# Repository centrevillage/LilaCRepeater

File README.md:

# LilaCRepeater
Eurorack sample looping module driven by Daisy (https://www.electro-smith.com/daisy)

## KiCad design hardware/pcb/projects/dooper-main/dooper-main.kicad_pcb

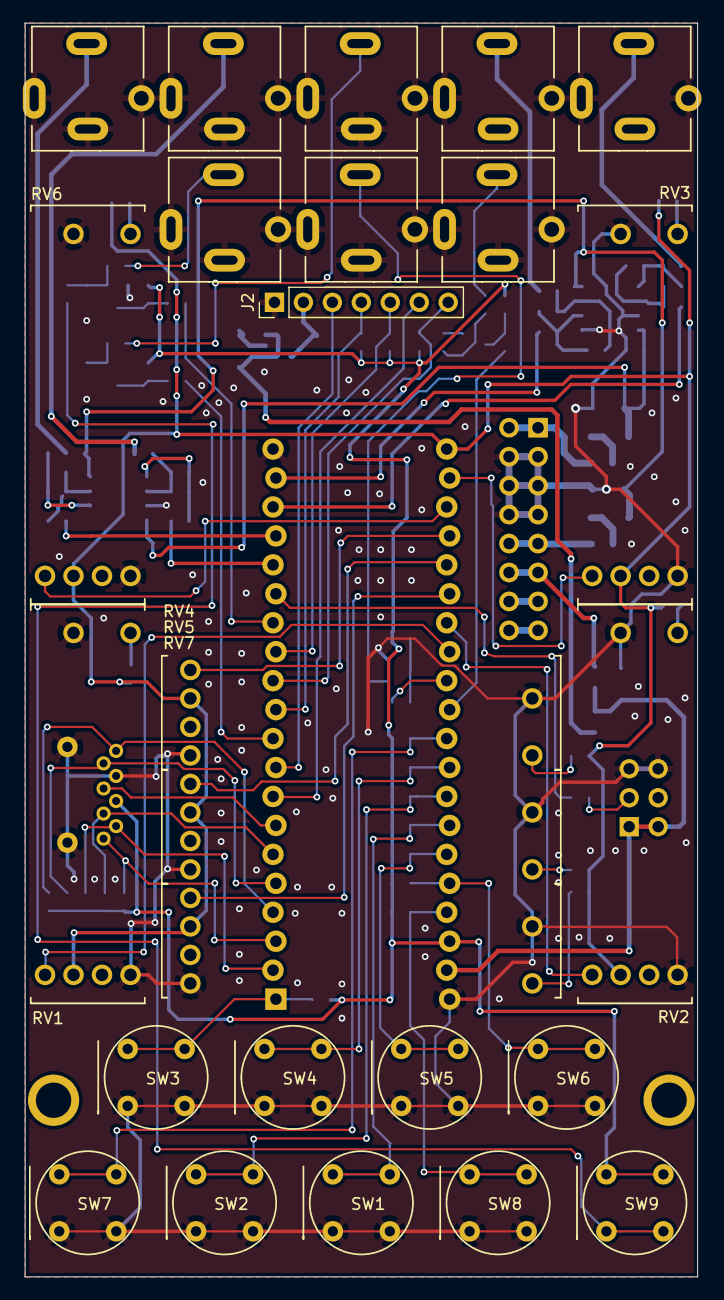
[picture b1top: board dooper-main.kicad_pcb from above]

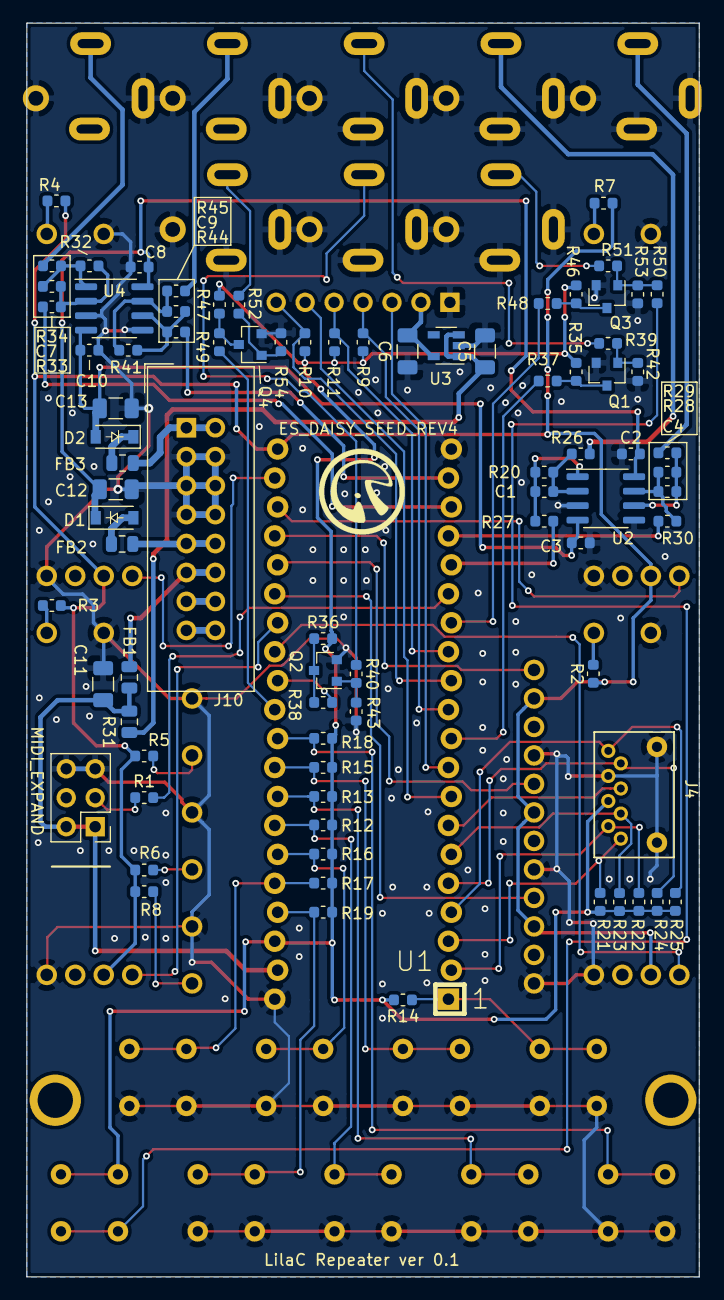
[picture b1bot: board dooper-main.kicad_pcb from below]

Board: 2 copper layers, 59.0 x 110.0 mm, 110 parts (83 on the bottom side), 83 nets.

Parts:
C1, C4, C7, C9: 18p; C_0603_1608Metric
C2, C3, C8, C10: 100n; C_0603_1608Metric
C5, C6, C11, C12, C13: 22u; C_1206_3216Metric
D1, D2: 1N5158; D_SOD-123_1n4148_mod
FB1, FB2, FB3: 600; R_0805_2012Metric
H1, H1#2: M3_Hole; M3_GND_HOLE_MINI
J1: Conn_02x03_Odd_Even; PinHeader_2x03_P2.54mm_Vertical
J2: Conn_01x07; PinHeader_1x07_P2.54mm_Vertical
J3, J5, J6, J7, J8, J9, J11, J12: PJ301BM; PJ301BM_oval_smallpad
J4: Micro_SD_Card; MICRO_SD_VERTICAL
J10: Conn_02x08_Odd_Even; IDC-Header_2x08_P2.54mm_Vertical
Q1, Q2, Q3, Q4: MMBT3904; SOT-23
R1: 47; R_0603_1608Metric
R2, R3, R4, R5, R6, R7, R8, R9, R10, R11, R12, R13, R14, R15, R16, R17, R18, R19, R20, R28, R33, R35, R36, R44, R46, R47: 10k; R_0603_1608Metric
R21, R22, R23, R24, R25: 47k; R_0603_1608Metric
R26, R29, R32, R39, R40, R41, R42, R43, R50, R51, R52, R53, R54: 100k; R_0603_1608Metric
R27, R30, R34, R37, R38, R45, R48, R49: 470; R_0603_1608Metric
R31: 10; R_0805_2012Metric
RV1, RV2, RV3, RV4, RV5, RV6, RV7: SLIDER; BOURNS_SLIDER_20mm
SW1, SW2, SW3, SW4, SW5, SW6, SW7, SW8, SW9: SW_Push; CandK_Comp_Button
U1: ES_DAISY_SEED_REV4; ES_DAISY_SEED
U2, U4: OPA2134; SOIC-8_3.9x4.9mm_P1.27mm
U3: LDK320; SOT-23-5

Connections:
+3.3VA: R2.1, R3.1, R4.1, R5.1, R6.1, R7.1, R8.1, RV1.1, RV2.1, RV3.1, RV4.1, RV5.1, RV6.1, RV7.1, U1.21
+3V3: J4.4, R9.1, R10.1, R11.1, R12.2, R13.2, R14.2, R15.2, R16.2, R17.2, R18.2, R19.2, R21.1, R22.1, R23.1, R24.1, R25.1, R35.2, R36.2, R46.2, R47.2, SW9.1, U1.38
+5V: C11.1, FB1.1, J1.1, J1.2, R31.2, U1.39
+12V: C2.2, C8.2, C12.1, D1.1, U2.8, U4.8
-12V: C3.2, C10.2, C13.2, D2.2, U2.4, U4.4
/CLEAR_BTN: R12.1, SW1.1, U1.34
/DG_AUDIO_IN_L: R27.1, U1.16
/DG_AUDIO_IN_R: R30.1, U1.17
/DG_AUDIO_OUT_L: R33.2, U1.18
/DG_AUDIO_OUT_R: R44.2, U1.19
/DRY_VOL: RV1.2, U1.28
/MUTE_BTN: R18.1, SW7.1, U1.31
/OLED_DC: J2.6, U1.8
/PAN: RV7.2, U1.26
/REC_TARGET_BTN: R13.1, SW2.1, U1.33
/REC_TRIG: R49.1, U1.30
/RESET_TRIG: R38.1, U1.29
/REVERSE_BTN: R19.1, SW8.1, U1.37
/RUN_TRIG: R48.1, U1.14
/SAMPLE_FDBK: RV6.2, U1.23
/SAMPLE_LENGTH: RV5.2, U1.25
/SAMPLE_SPEED: RV3.2, U1.22
/SAMPLE_START_POS: RV4.2, U1.24
/SD_CLK: J4.5, U1.7
/SD_CMD: J4.3, R23.2, U1.6
/SD_D0: J4.7, R24.2, U1.5
/SD_D1: J4.8, R25.2, U1.4
/SD_D2: J4.1, R21.2, U1.3
/SD_D3: J4.2, R22.2, U1.2
/SPI_MOSI: J2.4, R9.2, U1.11
/SPI_SCK: J2.3, U1.9
/SYNC_IN: R37.1, U1.10
/TRACK1_BTN: R14.1, SW3.1, U1.1
/TRACK2_BTN: R15.1, SW4.1, U1.32
/TRACK3_BTN: R16.1, SW5.1, U1.35
/TRACK4_BTN: R17.1, SW6.1, U1.36
/TRACK_VOL: RV2.2, U1.27
/USART_RX: R1.2, U1.15
/~OLED_CS: J2.7, R10.2, U1.12
/~OLED_RST: J2.5, R11.2, U1.13
GND: C2.1, C3.1, C5.2, C6.2, C8.1, C10.1, C11.2, C12.2, C13.1, J1.5, J1.6, J2.1, J3.1, J3.2, J3.3, J4.6, J4.9, J5.1, J5.2, J5.3, J6.1, J6.2, J7.1, J7.2, J7.3, J8.1, J8.2, J8.3, J9.1, J9.2, J10.3, J10.4, J10.5, J10.6, J10.7, J10.8, J11.1, J11.2, J11.3, J12.1, J12.2, J12.3, Q1.2, Q2.2, Q3.2, Q4.2, R42.1, R43.1, R53.1, R54.1, RV1.3, RV1.5, RV2.3, RV2.5, RV3.3, RV3.5, RV4.3, RV4.5, RV5.3, RV5.5, RV6.3, RV6.5, RV7.3, RV7.5, SW1.2, SW2.2, SW3.2, SW4.2, SW5.2, SW6.2, SW7.2, SW8.2, U1.20, U1.40, U2.3, U2.5, U3.2, U4.3, U4.5
unnamed: C1.1, R20.1, R27.2, U2.1
unnamed: C1.2, R20.2, R26.1, U2.2
unnamed: C4.1, R28.1, R30.2, U2.7
unnamed: C4.2, R28.2, R29.1, U2.6
unnamed: C5.1, R31.1, U3.1, U3.3
unnamed: C7.1, R32.1, R34.2, U4.1
unnamed: C7.2, R32.2, R33.1, U4.2
unnamed: C9.1, R41.1, R45.2, U4.7
unnamed: C9.2, R41.2, R44.1, U4.6
unnamed: D1.2, FB2.1
unnamed: D2.1, FB3.1
unnamed: FB1.2, J10.11, J10.12
unnamed: FB2.2, J10.9, J10.10
unnamed: FB3.2, J10.1, J10.2
unnamed: J1.3, R1.1
unnamed: J3.4, R29.2
unnamed: J5.4, R26.2
unnamed: J6.4, R45.1
unnamed: J7.4, R39.2
unnamed: J8.4, R40.2
unnamed: J9.4, R34.1
unnamed: J10.13, J10.14
unnamed: J10.15, J10.16
unnamed: J11.4, R51.2
unnamed: J12.4, R52.2
unnamed: Q1.1, R39.1, R42.2
unnamed: Q1.3, R35.1, R37.2
unnamed: Q2.1, R40.1, R43.2
unnamed: Q2.3, R36.1, R38.2
unnamed: Q3.1, R50.1, R51.1, R53.2
unnamed: Q3.3, R46.1, R48.2
unnamed: Q4.1, R52.1, R54.2
unnamed: Q4.3, R47.1, R49.2
unnamed: R2.2, RV1.4
unnamed: R3.2, RV2.4
unnamed: R4.2, RV3.4
unnamed: R5.2, RV4.4
unnamed: R6.2, RV5.4
unnamed: R7.2, RV6.4
unnamed: R8.2, RV7.4
unnamed: R50.2, SW9.2
OLED_VCC: C6.1, J2.2, U3.5

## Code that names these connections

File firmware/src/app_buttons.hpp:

#ifndef LR_APP_BUTTONS_H
#define LR_APP_BUTTONS_H

#include <igb_stm32/periph/gpio.hpp>
#include <igb_daisy/periph/gpio.hpp>
#include <igb_sdk/ui/button.hpp>
#include <functional>
#include <array>

using namespace igb::stm32;
using namespace igb::sdk;
using namespace igb::daisy;

enum class AppBtnId : uint8_t {
  track1 = 0,
  track2,
  track3,
  track4,
  mute,
  rec,
  clear,
  rev,
  run,

  size
};

constexpr uint8_t button_count = 9;

struct AppButtons {
  uint16_t state_bits = 0;
  std::function<void(AppBtnId, bool)> on_change;

// hardware version 0.3 ~
#if 1
  ButtonMatrix<GpioPin, 3, GpioPin, 3> btn_matrix {
    .in_pins = {
      GpioPin::newPin(daisy_pin_to_stm32_pin(DaisyGpioPinType::p29)),
      GpioPin::newPin(daisy_pin_to_stm32_pin(DaisyGpioPinType::p30)),
      GpioPin::newPin(daisy_pin_to_stm32_pin(DaisyGpioPinType::p31)),
    },
    .out_pins = {
      GpioPin::newPin(daisy_pin_to_stm32_pin(DaisyGpioPinType::p26)),
      GpioPin::newPin(daisy_pin_to_stm32_pin(DaisyGpioPinType::p27)),
      GpioPin::newPin(daisy_pin_to_stm32_pin(DaisyGpioPinType::p28))
    }
  };
#endif
  
// hardware version 0.2 ~
#if 0
  ButtonSingle<GpioPin> mute_btn {
    GpioPin::newPin(daisy_pin_to_stm32_pin(DaisyGpioPinType::p25))
  };

  ButtonMatrix<GpioPin, 4, GpioPin, 2> btn_matrix {
    .in_pins = {
      GpioPin::newPin(daisy_pin_to_stm32_pin(DaisyGpioPinType::p28)),
      GpioPin::newPin(daisy_pin_to_stm32_pin(DaisyGpioPinType::p29)),
      GpioPin::newPin(daisy_pin_to_stm32_pin(DaisyGpioPinType::p30)),
      GpioPin::newPin(daisy_pin_to_stm32_pin(DaisyGpioPinType::p31))
    },
    .out_pins = {
      GpioPin::newPin(daisy_pin_to_stm32_pin(DaisyGpioPinType::p26)),
      GpioPin::newPin(daisy_pin_to_stm32_pin(DaisyGpioPinType::p27))
    }
  };
#endif

// hardware version 0.1
#if 0
  // TODO: button matrix (fix hardware)
  ButtonSingle<GpioPin> mute_btn {
    GpioPin::newPin(daisy_pin_to_stm32_pin(DaisyGpioPinType::p25))
  };
  ButtonSingle<GpioPin> rec_btn {
    GpioPin::newPin(daisy_pin_to_stm32_pin(DaisyGpioPinType::p27))
  };
  ButtonSingle<GpioPin> clear_btn {
    GpioPin::newPin(daisy_pin_to_stm32_pin(DaisyGpioPinType::p28))
  };
  ButtonSingle<GpioPin> rev_btn {
    GpioPin::newPin(daisy_pin_to_stm32_pin(DaisyGpioPinType::p31))
  };
  // TODO: テンプレートパラメータでbool値を渡した時の挙動が変？
  //ButtonSingle<GpioPin, false> run_btn {
  ButtonSingle<GpioPin> run_btn {
    GpioPin::newPin(daisy_pin_to_stm32_pin(DaisyGpioPinType::p14))
  }; // pull down
  ButtonSingle<GpioPin> track1_btn {
    GpioPin::newPin(daisy_pin_to_stm32_pin(DaisyGpioPinType::p1))
  };
  ButtonSingle<GpioPin> track2_btn {
    GpioPin::newPin(daisy_pin_to_stm32_pin(DaisyGpioPinType::p26))
  };
  ButtonSingle<GpioPin> track3_btn {
    GpioPin::newPin(daisy_pin_to_stm32_pin(DaisyGpioPinType::p29))
  };
  ButtonSingle<GpioPin> track4_btn {
    GpioPin::newPin(daisy_pin_to_stm32_pin(DaisyGpioPinType::p30))
  };
#endif

  void init() {
// hardware version 0.3 ~
#if 1
    for (auto& in_pin : btn_matrix.in_pins) {
      in_pin.enable();
      in_pin.initInput(GpioPullMode::no, GpioSpeedMode::high);
    }
    for (auto& out_pin : btn_matrix.out_pins) {
      out_pin.enable();
      out_pin.initOutput(GpioOutputMode::pushpull, GpioSpeedMode::high);
    }
    btn_matrix.init();
#endif

// hardware version 0.2 ~
#if 0
    mute_btn.pin.enable();
    mute_btn.pin.initInput(GpioPullMode::UP, GpioSpeedMode::HIGH);

    for (auto& in_pin : btn_matrix.in_pins) {
      in_pin.enable();
      in_pin.initInput(GpioPullMode::NO, GpioSpeedMode::HIGH);
    }
    for (auto& out_pin : btn_matrix.out_pins) {
      out_pin.enable();
      out_pin.initOutput(GpioOutputMode::PUSHPULL, GpioSpeedMode::HIGH);
    }
    btn_matrix.init();
#endif

// hardware version 0.1
#if 0
    mute_btn.pin.enable();
    mute_btn.pin.initInput(GpioPullMode::UP, GpioSpeedMode::HIGH);

    rec_btn.pin.enable();
    rec_btn.pin.initInput(GpioPullMode::UP, GpioSpeedMode::HIGH);

    clear_btn.pin.enable();
    clear_btn.pin.initInput(GpioPullMode::UP, GpioSpeedMode::HIGH);

    rev_btn.pin.enable();
    rev_btn.pin.initInput(GpioPullMode::UP, GpioSpeedMode::HIGH);

    run_btn.pin.enable();
    run_btn.pin.initInput(GpioPullMode::UP, GpioSpeedMode::HIGH);

    track1_btn.pin.enable();
    track1_btn.pin.initInput(GpioPullMode::UP, GpioSpeedMode::HIGH);

    track2_btn.pin.enable();
    track2_btn.pin.initInput(GpioPullMode::UP, GpioSpeedMode::HIGH);

    track3_btn.pin.enable();
    track3_btn.pin.initInput(GpioPullMode::UP, GpioSpeedMode::HIGH);

    track4_btn.pin.enable();
    track4_btn.pin.initInput(GpioPullMode::UP, GpioSpeedMode::HIGH);
#endif
  }

  bool isOn(AppBtnId btn_id) {
    bool on = false;
// hardware version 0.3 ~
#if 1
    switch (btn_id) {
      case AppBtnId::track1:
        on = btn_matrix.isOn(0, 0);
        break;
      case AppBtnId::track2:
        on = btn_matrix.isOn(1, 0);
        break;
      case AppBtnId::track3:
        on = btn_matrix.isOn(2, 0);
        break;
      case AppBtnId::mute:
        on = btn_matrix.isOn(0, 1);
        break;
      case AppBtnId::rec:
        on = btn_matrix.isOn(1, 1);
        break;
      case AppBtnId::track4:
        on = btn_matrix.isOn(2, 1);
        break;
      case AppBtnId::clear:
        on = btn_matrix.isOn(0, 2);
        break;
      case AppBtnId::rev:
        on = btn_matrix.isOn(1, 2);
        break;
      case AppBtnId::run:
        on = btn_matrix.isOn(2, 2);
        break;
      default:
        break;
    }
#endif

// hardware version 0.2 ~
#if 0
    switch (btn_id) {
      case AppBtnId::mute:
        on = mute_btn.isOn();
        break;
      case AppBtnId::track1:
        on = btn_matrix.isOn(0, 0);
        break;
      case AppBtnId::track2:
        on = btn_matrix.isOn(1, 0);
        break;
      case AppBtnId::track3:
        on = btn_matrix.isOn(2, 0);
        break;
      case AppBtnId::track4:
        on = btn_matrix.isOn(3, 0);
        break;
      case AppBtnId::rec:
        on = btn_matrix.isOn(0, 0);
        break;
      case AppBtnId::clear:
        on = btn_matrix.isOn(0, 1);
        break;
      case AppBtnId::rev:
        on = btn_matrix.isOn(0, 2);
        break;
      case AppBtnId::run:
        on = btn_matrix.isOn(0, 3);
        break;
      default:
        break;
    }
#endif

// hardware version 0.1
#if 0
    switch (btn_id) {
      case AppBtnId::mute:
        on = mute_btn.isOn();
        break;
      case AppBtnId::track1:
        on = track1_btn.isOn();
        break;
      case AppBtnId::track2:
        on = track2_btn.isOn();
        break;
      case AppBtnId::track3:
        on = track3_btn.isOn();
        break;
      case AppBtnId::track4:
        on = track4_btn.isOn();
        break;
      case AppBtnId::rec:
        on = rec_btn.isOn();
        break;
      case AppBtnId::clear:
        on = clear_btn.isOn();
        break;
      case AppBtnId::rev:
        on = rev_btn.isOn();
        break;
      case AppBtnId::run:
        on = run_btn.isOn();
        break;
      default:
        break;
    }
#endif

    return on;
  }

  bool process() {
// hardware version 0.3 ~
#if 1
    btn_matrix.process();
#endif

// hardware version 0.2 ~
#if 0
    mute_btn.process();
    btn_matrix.process();
#endif

// hardware version 0.1
#if 0
    track1_btn.process();
    track2_btn.process();
    track3_btn.process();
    track4_btn.process();
    mute_btn.process();
    rec_btn.process();
    clear_btn.process();
    rev_btn.process();
    run_btn.process();
#endif

    uint16_t new_bits = 0;
    for (uint8_t i = 0; i < static_cast<uint8_t>(AppBtnId::size); ++i) {
      if (isOn(static_cast<AppBtnId>(i))) {
        new_bits |= (uint16_t)1 << i;
      }
    }
    if (state_bits != new_bits) {
      if (on_change) {
        uint16_t diff_bits = state_bits ^ new_bits;
        state_bits = new_bits;
        for (uint8_t i = 0; i < static_cast<uint8_t>(AppBtnId::size); ++i) {
          if (diff_bits & ((uint16_t)1 << i)) {
            on_change(static_cast<AppBtnId>(i), !!(new_bits & ((uint16_t)1 << i)));
          }
        }
      }
      return true;
    }
    return false;
  }
};

extern AppButtons buttons;

#endif /* LR_APP_BUTTONS_H */

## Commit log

2020-06-21 ver 0.1
2020-11-14 add submodules
2020-11-14 add test program
2020-11-22 change target name
2020-11-22 update libDaisy
2020-11-22 ignore submodule dirty
2020-11-22 add igb_sdk
2020-12-19 とりあえず画面表示ができるとこまで
2020-12-19 ignore dirty
2020-12-27 refactoring
2020-12-28 add looper
2021-01-01 サンプリングのテスト
2021-01-03 change hardware version to 0.2
2021-01-05 fix normal view
2021-01-08 fix README.md
2021-01-18 ステレオサンプル化
2021-01-18 implement non-quantized rec
2021-01-23 hardware version is changed to 0.3
2021-01-24 add test mode
2021-01-26 view ext sync state
2021-01-26 bugfix
2021-01-27 fix analog input ranges of sliders
2021-06-29 update igb_sdk lib
